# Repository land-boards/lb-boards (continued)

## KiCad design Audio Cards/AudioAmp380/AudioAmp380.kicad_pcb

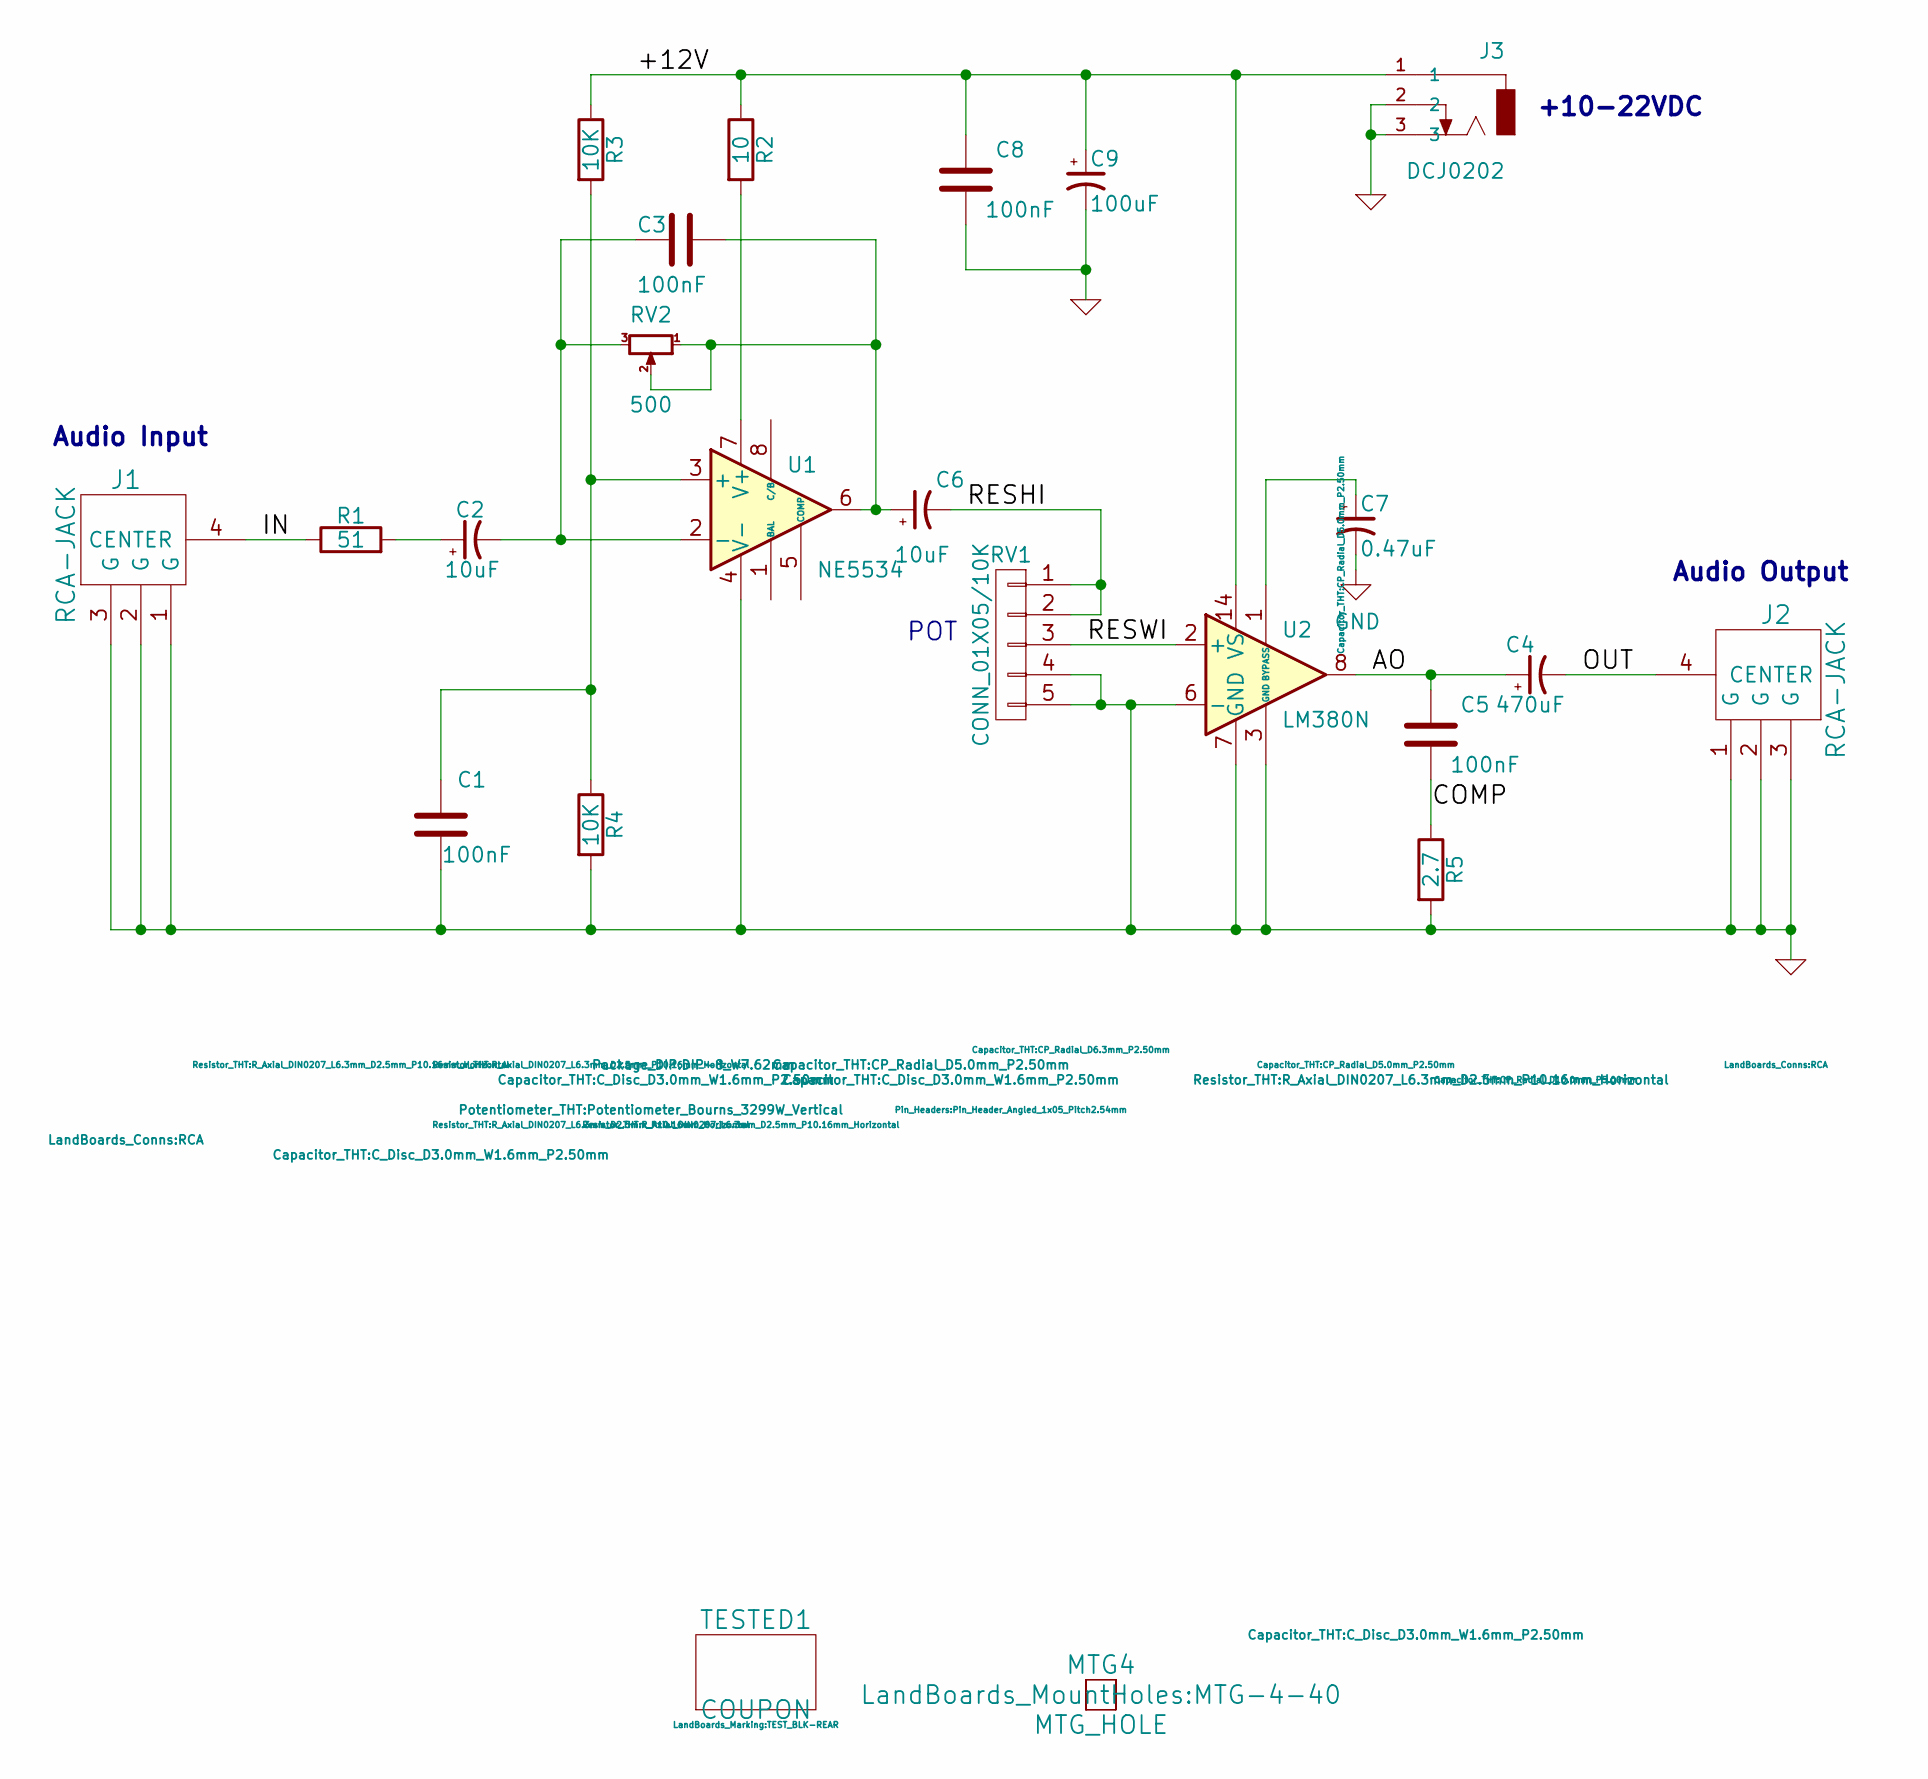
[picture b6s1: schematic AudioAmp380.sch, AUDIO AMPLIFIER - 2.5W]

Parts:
C1, C3, C5, C8: 100nF; C_Disc_D3.0mm_W1.6mm_P2.50mm; MfgPN 1C10Z5U104M050B
C2: 10uF; CP_Radial_D5.0mm_P2.50mm
C4: 470uF; CP_Radial_D10.0mm_P5.00mm
C6: 10uF; CP_Radial_D5.0mm_P2.50mm; MfgPN 1C10Z5U104M050B
C7: 0.47uF; CP_Radial_D5.0mm_P2.50mm
C9: 100uF; CP_Radial_D6.3mm_P2.50mm
J1, J2: RCA-JACK; RCA; MfgPN NYS354
J3: DCJ0202; DCJ-NEW-Slotted
MTG4: MTG_HOLE; MTG-4-40
R1: 51; R_Axial_DIN0207_L6.3mm_D2.5mm_P10.16mm_Horizontal
R2: 10; R_Axial_DIN0207_L6.3mm_D2.5mm_P10.16mm_Horizontal
R3, R4: 10K; R_Axial_DIN0207_L6.3mm_D2.5mm_P10.16mm_Horizontal
R5: 2.7; R_Axial_DIN0207_L6.3mm_D2.5mm_P10.16mm_Horizontal; MfgPN CCF0710R0GKE36
RV1: CONN_01X05/10K; Pin_Header_Angled_1x05_Pitch2.54mm
RV2: 500; Potentiometer_Bourns_3299W_Vertical
TESTED1: COUPON; TEST_BLK-REAR
U1: NE5534; DIP-8_W7.62mm
U2: LM380N; DIP-14_W7.62mm

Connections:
/+12V: C8.2, C9.1, J3.1, R2.1, R3.1, U2.14 (VS)
/AO: C4.1, C5.2, U2.8
/COMP: C5.1, R5.1
/IN: J1.4 (CENTER), R1.1
/OUT: C4.2, J2.4 (CENTER)
/RESHI: C6.2, RV1.1, RV1.2
/RESWI: RV1.3, U2.2 (+)
GND: C1.2, C7.2, C8.1, C9.2, J1.1 (G), J1.2 (G), J1.3 (G), J2.1 (G), J2.2 (G), J2.3 (G), J3.2, J3.3, R4.2, R5.2, RV1.4, RV1.5, U1.4 (V-), U2.3 (GND), U2.4 (GND), U2.5 (GND), U2.6 (-), U2.7 (GND), U2.10 (GND), U2.11 (GND), U2.12 (GND)
unnamed: C1.1, R3.2, R4.1, U1.3 (+)
unnamed: C2.1, R1.2
unnamed: C2.2, C3.2, RV2.3, U1.2 (-)
unnamed: C3.1, C6.1, RV2.1, RV2.2, U1.6
unnamed: C7.1, U2.1 (BYPASS)
unnamed: R2.2, U1.7 (V+)

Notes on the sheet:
POT
+10-22VDC
Audio Input
Audio Output

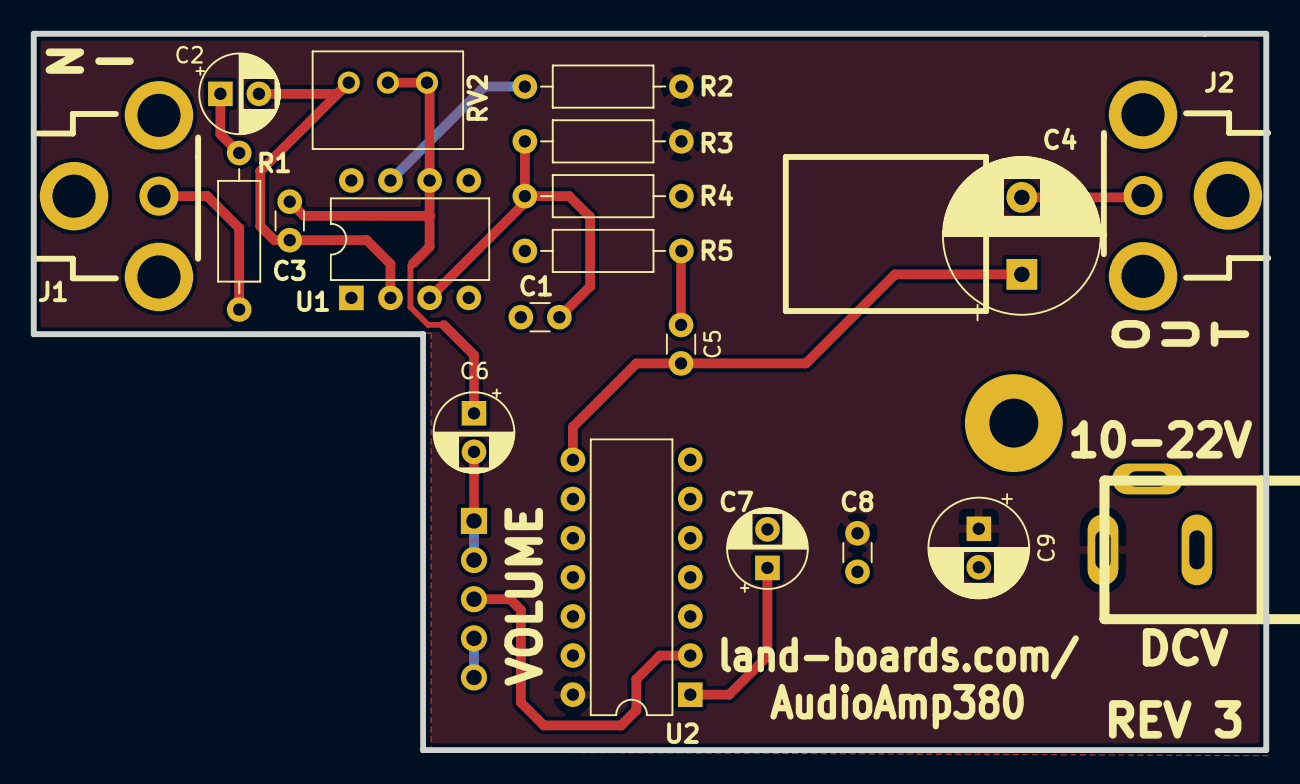
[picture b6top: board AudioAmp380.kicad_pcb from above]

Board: 2 copper layers, 80.0 x 46.5 mm, 23 parts (1 on the bottom side), 14 nets.
